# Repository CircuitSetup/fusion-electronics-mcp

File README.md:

# Fusion Electronics MCP & AI PCB Builder

Build complete PCB candidates with an AI coding assistant using the **offline EAGLE compiler**. The assistant writes a JSON design spec, then compiles the schematic, board outline, and component placement, routes the board, and reviews HTML/SVG previews and validation results. All of that runs with Fusion closed.

**Start offline for new boards.** Compiling a design in batches is faster than building it through individual live MCP calls because it avoids repeated round trips to Fusion for placement, wiring, and routing. Use the Fusion Electronics MCP tools to import the reviewed candidate as a linked Electronics Design, run native checks, and make targeted edits in Fusion.

- [Build a new board offline](#build-a-new-board-offline)
- [Features](#features)
- [Quick start](#quick-start)
- [Documentation](#documentation)
- [Configuration](#configuration)

*A dual CRPS power-supply backplane built with this server, from schematic capture through placement, routing, and manufacturing review.*

<table>
<tr>
<td width="50%"><br>Schematic</td>
<td width="50%"><br>PCB layout</td>
</tr>
<tr>
<td width="50%"><br>Installed board</td>
<td width="50%"><br>Assembly preview</td>
</tr>
</table>

## Features

- **Offline PCB builder for AI tools:** Compile a JSON design spec, local templates, and libraries into paired `.sch` and `.brd` files. Plan and review routing, validate the candidate, and import the reviewed result into Fusion.
- **Schematic design:** Place parts and multi-unit symbols, organize functional blocks and sheets, and connect pins with continuous right-angle wires. Preview batch edits and reusable circuit blocks before applying them.
- **Placement and routing:** Arrange support components around ICs, align inline parts, and move components in batches. Route individual nets, differential pairs, parallel buses, and remaining connections; add copper pours, ground vias, and stitching.
- **Keepouts:** Route around supported package and board restrictions, define explicitly authorized header connection corridors, and preflight library keepout changes. Corridors affect offline planning only and do not waive native DRC.
- **Design checks:** Inspect parts, nets, placement, ERC/DRC findings, annular rings, solder mask, and pour clearances. Check differential-pair lengths, estimate impedance and trace widths, and compare designs with reviewed datasheet evidence and project requirements.
- **Parts and libraries:** Search Fusion libraries and the local component catalog. Create symbols and device mappings from KiCad footprints, add package variants and STEP models, and update parts and models in existing designs.
- **Design reuse:** Import schematic connectivity, placement, and routing from KiCad boards. Reuse reviewed circuit blocks with explicit ports and separate internal nets.
- **Manufacturing preparation:** Use bundled JLCPCB rules and two-, four-, and six-layer stackups. Export BOM/CPL files, check assembly orientation, and compare exported Gerbers with the design.
- **Fusion automation and inspection:** Run reviewed ULPs and trusted scripts, manage add-ins, inspect selections and commands, and read lifecycle events. Inspect 3D bodies and measure interference and clearance.

List the available tools with:

```bash
fusion-electronics-mcp tools
```

## Quick start

### 1. Install the server

Requires **Python 3.12+** and **Git**. Live editing and native import also require Autodesk Fusion desktop on Windows or macOS. Use server **0.4.0+** and bundled add-in **0.14.23+** for the compiler/import workflow.

```bash
git clone https://github.com/CircuitSetup/fusion-electronics-mcp.git
cd fusion-electronics-mcp
python -m pip install .
fusion-electronics-mcp --version
```

The base install includes offline HTML/SVG previews. To add live board rendering and PDF inspection:

```bash
python -m pip install ".[render,documents]"
```

### 2. Connect your MCP client

Register `fusion-electronics-mcp` as a local stdio server. For clients that use an `mcpServers` configuration:

```json
{
  "mcpServers": {
    "fusion-electronics": {
      "command": "fusion-electronics-mcp"
    }
  }
}
```

Use the executable's absolute path if your client cannot find it on `PATH`. In Claude Code, you can register it with:

```bash
claude mcp add fusion-electronics -- fusion-electronics-mcp
```

### 3. Connect Fusion

Skip this step for offline work.

```bash
fusion-electronics-mcp install-addin
```

In Fusion, open **Utilities > Add-Ins > Scripts and Add-Ins**, select **FusionElectronicsMCP** on the **Add-Ins** tab, and click **Run**. Enable **Run on Startup** if desired.

Run `fusion-electronics-mcp doctor`, then call `get_context()` from your MCP client to confirm the connection and active design.

When updating, reinstall the package, run `install-addin --force`, stop and restart the add-in, and reconnect your MCP client. Fusion's built-in MCP server is also supported for compatible live operations; paired import requires the bundled add-in.

## Workflows

### Build a new board offline

Give your AI assistant the [detailed offline compiler instructions](docs/offline-compiler.md) and the [LED switch example](tests/fixtures/compiler/minimal/design.json). Have it draft the design spec, run the compiler from the terminal, and iterate on placement and routing using the preview and validation report.

1. **Prepare the specification.** Define the outline, parts, placements, and nets. Reference empty EAGLE schematic/board templates and local `.lbr` files using absolute paths and SHA-256 hashes. The board template supplies the stackup and design rules.
2. **Compile.** Run `compile-candidate` to generate `candidate.sch`, `candidate.brd`, a preview, a validation report, and a manifest.
3. **Route and review.** Use `route-candidate` to plan routing, inspect its preview and diagnostics, then promote the saved result to a new candidate. Keep each manifest path and its returned hash together.
4. **Validate and import.** Use `render-candidate` and `validate-candidate` to review the final preview and findings. Required `fail` or `unverified` findings block import. Set `routing.require_fully_routed` when all connections must be routed.

Pass the final manifest path and hash to `import_eagle_candidate` through MCP. If your assistant uses MCP for the build itself, the offline tools below run the same compiler with Fusion closed. Call `get_offline_compiler_workflow()` to locate the schema and workspace, then use a fresh output directory within that workspace.

| Step | MCP tools |
| --- | --- |
| Compile | `compile_eagle_candidate` |
| Plan and publish routing | `plan_eagle_candidate_routing`, `promote_eagle_candidate_routing` |
| Review | `render_eagle_candidate`, `validate_eagle_candidate` |
| Import | `import_eagle_candidate` |

Before import, save all open Fusion documents and clear pending edits and dialogs. Supply the reviewed manifest and hash, the active project ID, an existing destination folder, an unused design name, and one fresh 32-character lowercase hex request ID.

For `pending`, follow `next_action` and resume with the same arguments. Windows supports automated native file selection; on macOS, select the returned staged schematic and board. `saved_linked` confirms completion. For `state_unknown`, inspect `get_eagle_pair_import_status(request_id)` and Fusion before continuing.

After import, refill polygons where needed, run native ERC/DRC, and inspect airwires, footprints, placement, routing, and 3D models. Offline validation does not replace native or manufacturing review.

### Work on an existing Fusion design

Open the design and call `get_context()` to confirm the document and editor. Use `get_eagle_command_guide()` for supported tools, Electronics commands, and scripts.

For reviewed schematic changes:

1. Call `preview_schematic_edits` or `preview_circuit_block` to generate a preview and plan without changing CAD.
2. Review the proposed sheets, wiring, pin mappings, and before/after changes.
3. Explicitly authorize the exact plan, then apply it with `apply_schematic_plan`.
4. Review the result and run schematic checks and ERC before saving.

Plans reject changed source state and verify each operation. Applying a plan does not save the design. If a timeout, dialog, or mismatch returns `state_unknown`, inspect the result before retrying or undoing. This preview/apply workflow applies to the designated plan tools; other tools retain their own interfaces.

Example requests:

- “Review the schematic for unconnected power pins and wiring problems.”
- “Place the decoupling capacitors around U1 and show the proposed placement.”
- “Check the USB and Ethernet differential-pair lengths and impedance.”
- “Route USB_DP/USB_DN as a 90-ohm pair, matched to 0.1 mm.”
- “Export the JLCPCB BOM and CPL, then check the Gerber ZIP.”

### Import a local EAGLE schematic and board

For an existing pair, use `start_eagle_pair_import` with absolute, same-directory, same-basename `.sch`/`.brd` paths, their SHA-256 hashes, and an explicit destination. Save all open documents first and use one fresh request ID throughout.

Select the staged schematic and board in Fusion, then call `finish_eagle_pair_import`. The importer verifies connectivity and linked document identities before saving. Check progress with `get_eagle_pair_import_status`; an uncertain result must be resolved before starting another import. Hierarchical EAGLE modules are unsupported.

## Libraries and datasheets

Use `search_fusion_libraries` to search Fusion's locally indexed libraries, including inactive entries. Download missing libraries and activate the selected library in Library Manager before placement. `search_library` searches the MCP's separate JSON component catalog.

For custom parts, use a verified KiCad footprint with `create_library_part`, then insert it into an active Fusion library with `insert_library_part`. Save the library before attaching a STEP model where supported, and close it before placing its parts.

Custom definitions support grouped pins, multiple units, package variants, and datasheet references. Multi-unit parts use gate-qualified pins and explicit unit placement; automatic block layout does not support them. Include the full pinout, including NC/DNC and exposed pads. Use `check_datasheet_pins` and `check_project_requirements` to compare the design with reviewed evidence; missing, stale, or unreviewed evidence cannot pass.

Keep project-specific definitions and evidence outside the public repository. Set `FUSION_MCP_LIBRARY` for the default catalog, or pass `library_directory` for a single call.

Optional [Ground Plane Studio libraries](https://github.com/groundplane-studio/fusion-libraries) provide parts, JLCPCB attributes, frames, and power symbols. Upload their `.flbr` files to a Fusion project and enable them in Library Manager. Any compatible library can be used.

See the [datasheet workflow](docs/datasheet-workflow.md) for sourcing parts, inspecting documents, recording requirements, and preparing stackups.

## Manufacturing review

Export Gerbers manually from Fusion's CAM Processor, then run `check_gerbers`. Use `check_jlc_orientation` to compare assembly footprints and apply supported CPL rotation/offset corrections; uncertain matches are marked `needs_review`.

Before ordering, inspect every component in JLCPCB's placement preview, including pin 1, polarity, and pad alignment. Store corrections in the library's `JLC-ROTATION`, `JLC-X-OFFSET`, and `JLC-Y-OFFSET` attributes for future orders.

## Configuration

| Variable | Default | Purpose |
| --- | --- | --- |
| `FUSION_MCP_TRANSPORT` | `auto` | `addin`, `builtin`, or automatic selection, preferring the add-in |
| `FUSION_MCP_BUILTIN_URL` | `http://127.0.0.1:27182/mcp` | Fusion's built-in MCP endpoint |
| `FUSION_MCP_LIBRARY` | Per-user folder | Component library location |
| `FUSION_MCP_SHEET_FRAME` | None | Sheet frame as `DEVICE@LIBRARY` |
| `FUSION_MCP_GROUND_SYMBOL` | None | Ground symbol as `DEVICE@LIBRARY` |
| `FUSION_MCP_POWER_SYMBOL` | None | Power symbol as `DEVICE@LIBRARY`; value follows the rail name |
| `FUSION_MCP_KEEP_FOCUS` | `1` | Restore keyboard focus after Fusion takes it |
| `FUSION_MCP_LOCK_WAIT_S` | `30` | Seconds to wait for another MCP operation |
| `FUSION_MCP_DRC_AFTER_WRITES` | `1` | Check DRC before/after writes and report new errors |
| `FUSION_MCP_UNDO_ON_NEW_DRC` | `0` | Undo writes that introduce copper DRC errors when set to `1` |
| `FUSION_MCP_EASYEDA_CACHE` | Per-user folder | Downloaded footprint cache |
| `FUSION_MCP_EASYEDA_INTERVAL_S` | `15` | Minimum interval between EasyEDA requests |

The per-user data folder is `%LOCALAPPDATA%\fusion-electronics-mcp` on Windows and `~/Library/Application Support/fusion-electronics-mcp` on macOS.

## Safeguards and limitations

- **Routing needs review.** Whole-board routing still requires guidance. Confirm critical impedance estimates with your manufacturer's calculator.
- **Verification has boundaries.** Unsupported geometry is refused or reported as unverified. Native slot dimensions and CAM cuts require inspection. 3D checks cover currently loaded supported solids and cannot detect missing or outdated models.
- **Checks do not certify hardware.** Pin evidence and project topology checks do not establish electrical performance, creepage, insulation, or regulatory compliance.
- **Fusion compatibility varies.** On Fusion 2706.1.14, `new_design` refuses unverifiable document links and `attach_3d_model` refuses execution by default because of a known native crash. Create, link, and save new design families manually on that build.
- **The bridge is local.** The add-in listens on `127.0.0.1` with a per-session token. Compiler artifacts stay on local disk; imports save to the selected Fusion project. Optional footprint lookup downloads and caches EasyEDA data.
- **Scripts require trust.** Registered ULPs and scripts are not sandboxed. Legacy ULPs and scripts can change or save designs without guaranteed completion or rollback. Review their source before execution.
- **Uncertain operations need inspection.** Check Fusion before repeating an uncertain import, save, or autorouter operation. The dialog watchdog and focus guard are Windows-only.
- **External services are placeholders.** `request_design_review` and `get_assembly_quote` are stubs.

## Documentation

| Guide | Covers |
| --- | --- |
| [Offline compiler](docs/offline-compiler.md) | Specification, CLI/MCP workflow, routing, import, and native acceptance |
| [Fusion/EAGLE commands](server/fusion_mcp/data/eagle-command-guide.md) | Schematic, PCB, library, and script workflows |
| [Datasheet workflow](docs/datasheet-workflow.md) | Part sourcing, evidence, constraints, and stackup preparation |
| [Registered ULPs](docs/registered-ulps.md) | Source registration, reviewed edits, and legacy execution |
| [ULP probe](docs/ulp-probe.md) | Read-only inspection and result limits |
| [Architecture](docs/architecture.md) | Server/add-in design and Fusion integration behavior |

## Development

From the repository root:

```bash
python -m pip install -e ".[render,documents]"
python -m unittest discover -s tests
```

The [live tests](tests/live/) exercise a running Fusion instance. Run write tests only against disposable designs; CAD checks do not establish physical hardware performance.

## About and license

Created by [Ground Plane Studio](https://groundplanestudio.com/), a hardware development team covering industrial design, electronics, firmware, and manufacturing. [Contact the team](https://groundplanestudio.com/contact) for design, review, or production work.

Most of the code was written with Claude Code under engineering direction and review. This is an independent project, not affiliated with or endorsed by Autodesk, JLCPCB, or EasyEDA. Autodesk, Fusion, and EAGLE are trademarks of Autodesk, Inc.

Released under the [MIT License](LICENSE), without warranty. Review designs and manufacturing outputs before fabrication.

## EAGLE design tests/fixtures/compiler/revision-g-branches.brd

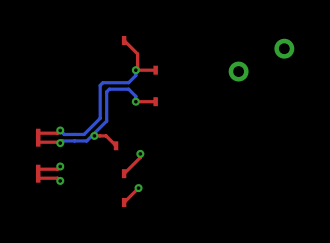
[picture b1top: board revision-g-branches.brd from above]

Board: 4 copper layers, 8 parts (0 on the bottom side), 4 nets.

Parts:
C45: C45
C46: C46
J7: J7
R49: R49
R50: R50
R52: R52
R53: R53
U10: U10

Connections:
ETH_RX_N: C46.1, R53.1, U10.5
ETH_RX_P: C45.1, R52.1, U10.6
ETH_TX_N: J7.2, R50.1, U10.1
ETH_TX_P: J7.1, R49.1, U10.2

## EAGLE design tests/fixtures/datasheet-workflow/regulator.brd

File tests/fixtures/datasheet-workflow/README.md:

# Synthetic regulator layout fixture

`regulator.brd` represents a synthetic eight-pad regulator with input/output capacitors, inductor, feedback divider and exposed-pad ground connections on a four-layer stack. `requirements.json` checks pad-specific supply/feedback proximity, switch-path length, power width/clearance and thermal-via connectivity. Engineering proximity bounds are explicitly assumptions. Implemented checks pass; the separate reference/return-path requirement deliberately remains unverified. This is not a fabrication-ready or electrically simulated converter.

`synthetic-evidence.json` is a test double, not manufacturer evidence or human approval. It cannot be bound as acquired evidence: there are no PDF manifests. Negative tests mutate evidence and geometry; production acquisition is documented in `docs/datasheet-workflow.md`.

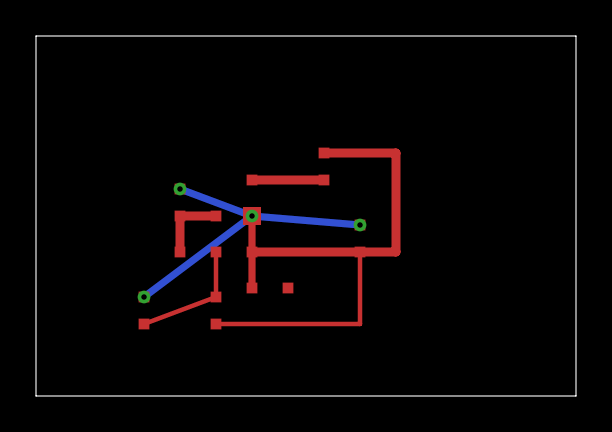
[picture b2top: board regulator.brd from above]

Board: 4 copper layers, 30.0 x 20.0 mm, 6 parts (0 on the bottom side), 5 nets.

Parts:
C1: 0805
C2: 22uF; 0805
L1: 2.2uH; 0805
R1: 100k; 0805
R2: 20k; 0805
U1: QFN

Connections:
FB: R1.2, R2.1, U1.FB
GND: C1.2, C2.2, R2.2, U1.AGND, U1.EP
SW: L1.1, U1.SW
VIN: C1.1, U1.EN, U1.VIN
VOUT: C2.1, L1.2, R1.1, U1.VOS
